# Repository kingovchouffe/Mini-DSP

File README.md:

# Mini-DSP

Mini-DSP is an audio-effects hardware and firmware project built around the
ES8388 audio codec and Raspberry Pi RP2350.

## Hardware

The KiCad designs include the main RP2350A/ES8388 board in
[`HW/Main`](HW/Main/) and an ES8388 test board in
[`Test board`](Test%20board/). They provide schematic and PCB references for
the codec, I2S audio interface, and supporting circuitry. See
[`HW/Main/README.md`](HW/Main/README.md) for hardware notes; confirm board
revisions and pin mappings before wiring.

## Software

[`SW/arduino_i2s_loopback`](SW/arduino_i2s_loopback/) contains an Arduino-Pico
full-duplex I2S sketch for the RP2350 and ES8388. It captures the mono input,
applies a time-based effect, and sends the result to the codec output. A
three-way DIP switch selects among bypass, chorus, flanger, delay, and reverb
presets. The effects and preset mapping are in separate header files.

See [`SW/README.md`](SW/README.md) for setup, wiring considerations, presets,
and build instructions.

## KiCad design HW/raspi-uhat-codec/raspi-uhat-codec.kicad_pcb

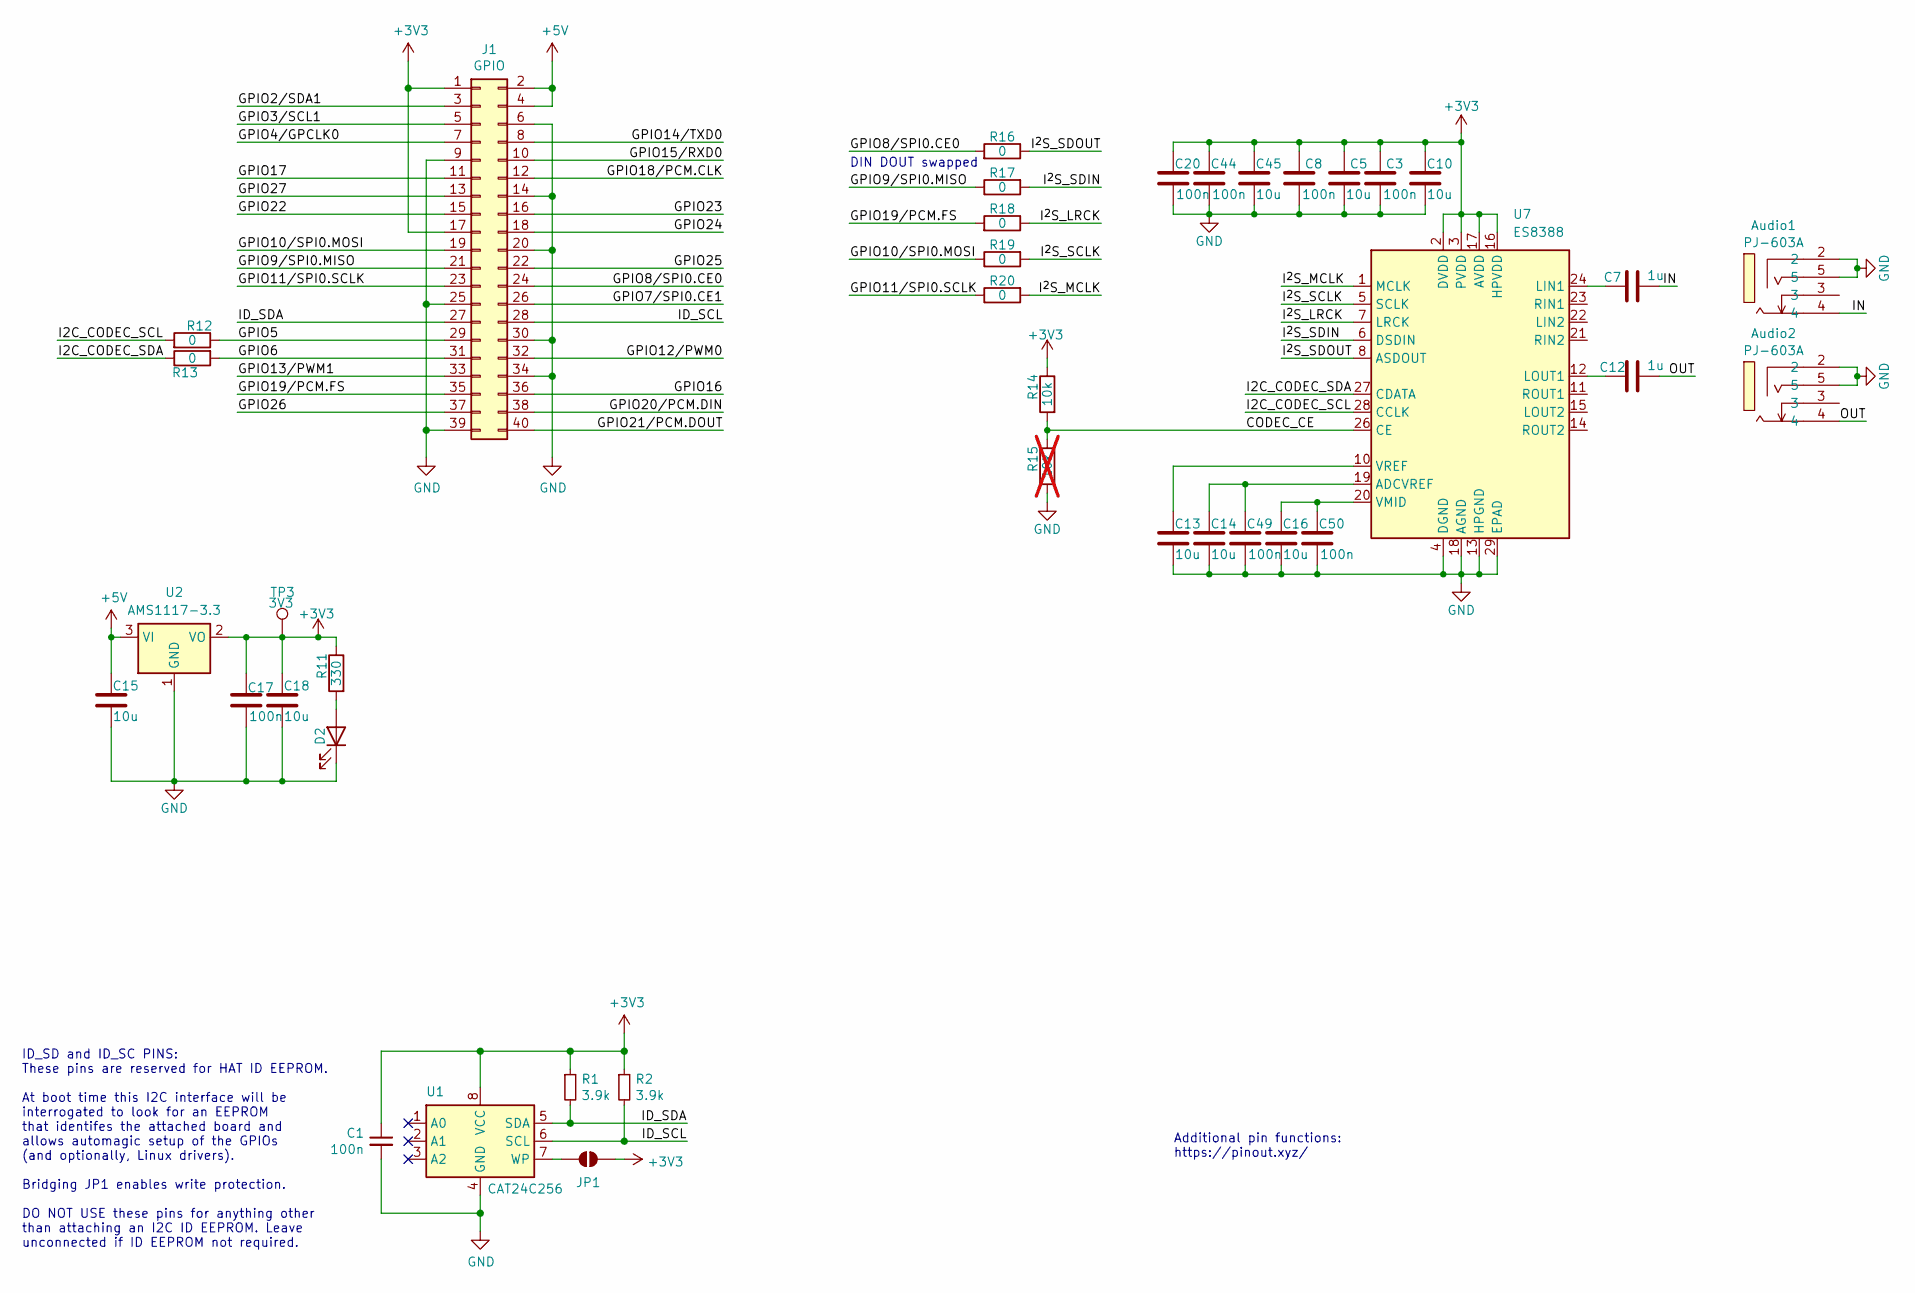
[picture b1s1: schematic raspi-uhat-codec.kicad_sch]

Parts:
Audio1, Audio2: PJ-603A; AUDIO-TH_PJ-603A_1; LCSC Part C309273
C1, C3, C8, C17, C20, C44, C49, C50: 100n; C_0603_1608Metric
C5, C10, C13, C14, C15, C16, C18, C45: 10u; C_0603_1608Metric
C7, C12: 1u; C_0805_2012Metric
D2: CTL1; LED_0805_2012Metric
J1: GPIO; PinSocket_2x20_P2.54mm_Vertical
JP1: ID_WP; SolderJumper-2_P1.3mm_Open_TrianglePad1.0x1.5mm
R1, R2: 3.9k; R_0603_1608Metric
R11: 330; R_0603_1608Metric
R12, R13, R16, R17, R18, R19, R20: 0; R_0603_1608Metric
R14: 10k; R_0603_1608Metric
R15: 10k; R_0603_1608Metric; not fitted
TP3: 3V3; TestPoint_Pad_D1.0mm
U1: CAT24C256; SOIC-8_3.9x4.9mm_P1.27mm
U2: AMS1117-3.3; SOT-223-3_TabPin2
U7: ES8388; QFN-28-1EP_4x4mm_P0.45mm_EP2.6x2.6mm

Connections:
+3V3: C1.1, C3.1, C5.1, C8.1, C10.1, C17.1, C18.1, C20.1, C44.1, C45.1, J1.1, J1.17, JP1.2 (B), R1.1, R2.1, R11.1, R14.1, TP3.1 (1_1), U1.8 (VCC), U2.2 (VO), U7.2 (DVDD), U7.3 (PVDD), U7.16 (HPVDD), U7.17 (AVDD)
+5V: C15.1, J1.2, J1.4, U2.3 (VI)
/CODEC_CE: R14.2, R15.1, U7.26 (CE)
/GPIO2/SDA1: J1.3
/GPIO3/SCL1: J1.5
/GPIO4/GPCLK0: J1.7
/GPIO5: J1.29, R12.1
/GPIO6: J1.31, R13.2
/GPIO7/SPI0.CE1: J1.26
/GPIO8/SPI0.CE0: J1.24, R16.2
/GPIO9/SPI0.MISO: J1.21, R17.1
/GPIO10/SPI0.MOSI: J1.19, R19.1
/GPIO11/SPI0.SCLK: J1.23, R20.1
/GPIO12/PWM0: J1.32
/GPIO13/PWM1: J1.33
/GPIO14/TXD0: J1.8
/GPIO15/RXD0: J1.10
/GPIO16: J1.36
/GPIO17: J1.11
/GPIO18/PCM.CLK: J1.12
/GPIO19/PCM.FS: J1.35, R18.2
/GPIO20/PCM.DIN: J1.38
/GPIO21/PCM.DOUT: J1.40
/GPIO22: J1.15
/GPIO23: J1.16
/GPIO24: J1.18
/GPIO25: J1.22
/GPIO26: J1.37
/GPIO27: J1.13
/I2C_CODEC_SCL: R12.2, U7.28 (CCLK)
/I2C_CODEC_SDA: R13.1, U7.27 (CDATA)
/ID_SCL: J1.28, R2.2, U1.6 (SCL)
/ID_SDA: J1.27, R1.2, U1.5 (SDA)
/IN: Audio1.4, C7.2
/I^{2}S_LRCK: R18.1, U7.7 (LRCK)
/I^{2}S_MCLK: R20.2, U7.1 (MCLK)
/I^{2}S_SCLK: R19.2, U7.5 (SCLK)
/I^{2}S_SDIN: R17.2, U7.6 (DSDIN)
/I^{2}S_SDOUT: R16.1, U7.8 (ASDOUT)
/OUT: Audio2.4, C12.2
GND: Audio1.2, Audio1.5, Audio2.2, Audio2.5, C1.2, C3.2, C5.2, C8.2, C10.2, C13.2, C14.2, C15.2, C16.2, C17.2, C18.2, C20.2, C44.2, C45.2, C49.2, C50.2, D2.1 (K), J1.6, J1.9, J1.14, J1.20, J1.25, J1.30, J1.34, J1.39, R15.2, U1.4 (GND), U2.1 (GND), U7.4 (DGND), U7.13 (HPGND), U7.18 (AGND), U7.29 (EPAD)
unnamed: D2.2 (A), R11.2
unnamed: JP1.1 (A), U1.7 (WP)
unnamed: C14.1, C49.1, U7.19 (ADCVREF)
unnamed: C7.1, U7.24 (LIN1)
unnamed: C12.1, U7.12 (LOUT1)
unnamed: C16.1, C50.1, U7.20 (VMID)
unnamed: C13.1, U7.10 (VREF)

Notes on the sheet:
ID_SD and ID_SC PINS: These pins are reserved for HAT ID EEPROM. At boot time this I2C interface will be interrogated to look for an EEPROM that identifes the attached board and allows automagic setup of the GPIOs (and optionally, Linux drivers). Bridging JP1 enables write protection. DO NOT USE th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
DIN DOUT swapped
Additional pin functions: https://pinout.xyz/

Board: 2 copper layers, 43 parts (1 on the bottom side), 29 nets, no tracks yet.

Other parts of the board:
MH1, MH2, MH3, MH4: MountingHole_2.7mm_M2.5

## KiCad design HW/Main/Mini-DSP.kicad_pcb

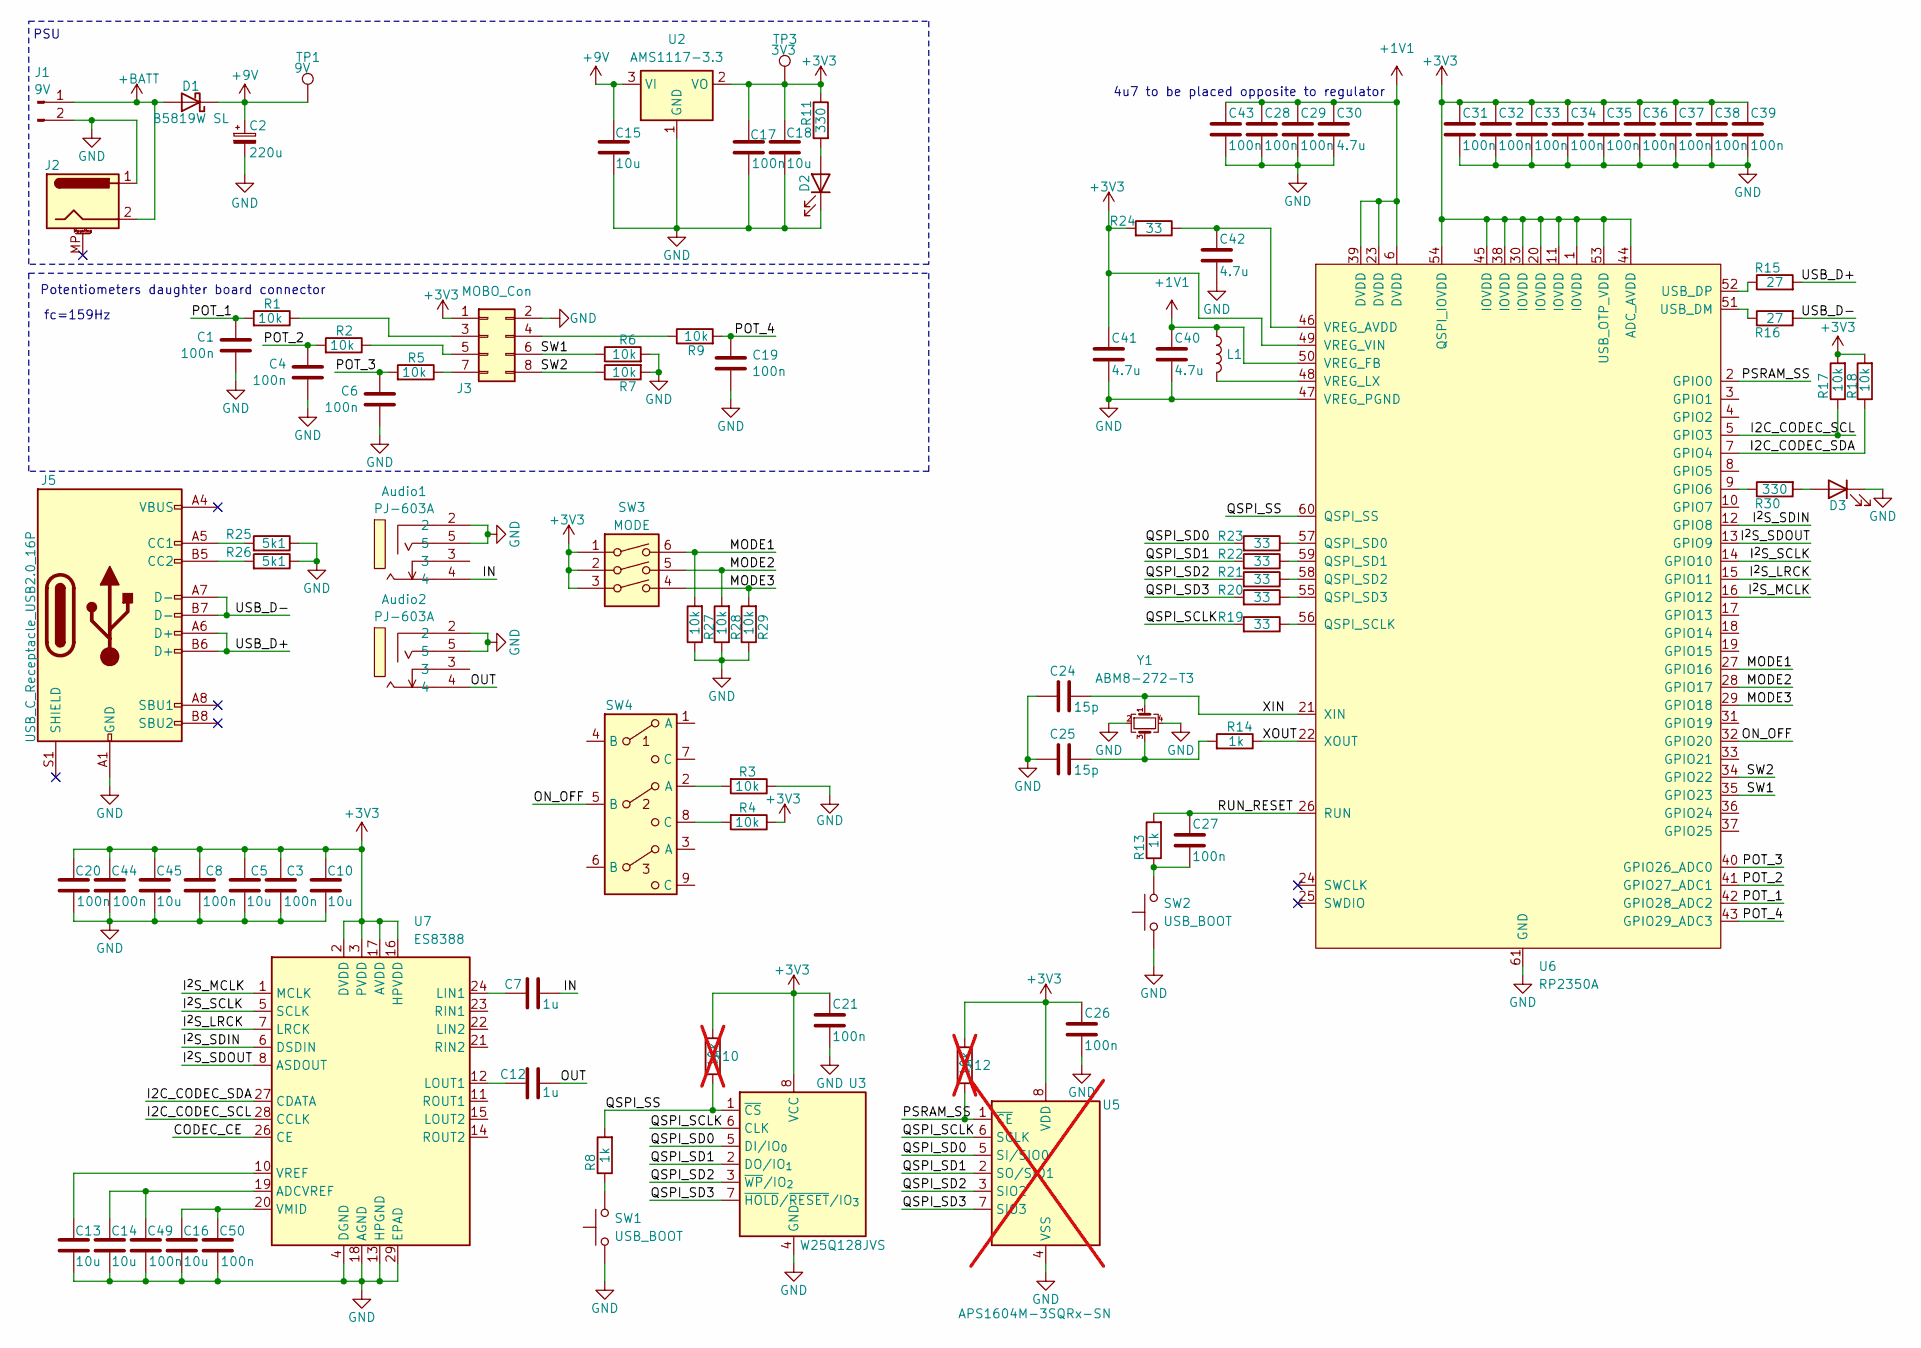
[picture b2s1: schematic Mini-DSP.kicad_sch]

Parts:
Audio1, Audio2: PJ-603A; AUDIO-TH_PJ-603A_1; LCSC Part C309273
C1, C3, C4, C6, C8, C17, C19, C20, C21, C26, C27, C28, C29, C31, C32, C33, C34, C35, C36, C37, C38, C39, C43, C44, C49, C50: 100n; C_0402_1005Metric
C2: 220u; CP_Elec_6.3x7.7
C5, C10, C13, C14, C15, C16, C18, C45: 10u; C_0603_1608Metric
C7, C12: 1u; C_0805_2012Metric
C24, C25: 15p; C_0402_1005Metric
C30, C40, C41, C42: 4.7u; C_0402_1005Metric
D1: B5819W SL; D_SOD-323; JLCPCB Part C8598
D2, D3: CTL1; LED_0603_1608Metric
J1: 9V; PinSocket_1x02_P2.54mm_Vertical
J2: Barrel_Jack_MountingPin; BarrelJack_Horizontal
J3: MOBO_Con; PinSocket_2x04_P2.54mm_Vertical
J5: USB_C_Receptacle_USB2.0_16P; USB_C_Receptacle_HCTL_HC-TYPE-C-16P-01A
L1: AOTA-B201610S3R3-101-T; L_Murata_DFE201610P
R1, R2, R3, R4, R5, R6, R7, R9, R17, R18, R27, R28, R29: 10k; R_0402_1005Metric
R8, R13, R14: 1k; R_0402_1005Metric
R10, R12: 10k; R_0402_1005Metric; not fitted
R11, R30: 330; R_0402_1005Metric
R15, R16: 27; R_0402_1005Metric
R19, R20, R21, R22, R23, R24: 33; R_0402_1005Metric
R25, R26: 5k1; R_0402_1005Metric
SW1, SW2: USB_BOOT; SW_SPST_TS-1088-xR020
SW3: MODE; SW_DIP_SPSTx03_Slide_KingTek_DSHP03TS_W7.62mm_P1.27mm
SW4: 3PDT_LED
TP1: 9V; TestPoint_Pad_D1.0mm
TP3: 3V3; TestPoint_Pad_D1.0mm
U2: AMS1117-3.3; SOT-223-3_TabPin2
U3: W25Q128JVS; SOIC-8_5.3x5.3mm_P1.27mm
U5: APS1604M-3SQRx-SN; SOIC-8_3.9x4.9mm_P1.27mm; not fitted
U6: RP2350A; QFN-60-1EP_7x7mm_P0.4mm_EP3.4x3.4mm_ThermalVias
U7: ES8388; QFN-28-1EP_4x4mm_P0.45mm_EP2.6x2.6mm
Y1: ABM8-272-T3; Crystal_SMD_3225-4Pin_3.2x2.5mm

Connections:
+1V1: C28.1, C29.1, C30.1, C40.1, C43.1, L1.1, U6.6 (DVDD), U6.23 (DVDD), U6.39 (DVDD), U6.50 (VREG_FB)
+3V3: C3.1, C5.1, C8.1, C10.1, C17.1, C18.1, C20.1, C21.1, C26.1, C31.1, C32.1, C33.1, C34.1, C35.1, C36.1, C37.1, C38.1, C39.1, C41.1, C44.1, C45.1, J3.1, R4.1, R10.2, R11.1, R12.2, R17.2, R18.2, R24.2, SW3.1, SW3.2, SW3.3, TP3.1 (1_1), U2.2 (VO), U3.8 (VCC), U5.8 (VDD), U6.1 (IOVDD), U6.11 (IOVDD), U6.20 (IOVDD), U6.30 (IOVDD), U6.38 (IOVDD), U6.44 (ADC_AVDD), U6.45 (IOVDD), U6.49 (VREG_VIN), U6.53 (USB_OTP_VDD), U6.54 (QSPI_IOVDD), U7.2 (DVDD), U7.3 (PVDD), U7.16 (HPVDD), U7.17 (AVDD)
+9V: C2.1, C15.1, D1.1 (K), TP1.1 (1_1), U2.3 (VI)
+BATT: D1.2 (A), J1.1, J2.2
/CODEC_CE: U7.26 (CE)
/I2C_CODEC_SCL: R17.1, U6.5 (GPIO3), U7.28 (CCLK)
/I2C_CODEC_SDA: R18.1, U6.7 (GPIO4), U7.27 (CDATA)
/IN: Audio1.4, C7.2
/I^{2}S_LRCK: U6.15 (GPIO11), U7.7 (LRCK)
/I^{2}S_MCLK: U6.16 (GPIO12), U7.1 (MCLK)
/I^{2}S_SCLK: U6.14 (GPIO10), U7.5 (SCLK)
/I^{2}S_SDIN: U6.12 (GPIO8), U7.6 (DSDIN)
/I^{2}S_SDOUT: U6.13 (GPIO9), U7.8 (ASDOUT)
/MODE1: R27.2, SW3.6, U6.27 (GPIO16)
/MODE2: R28.2, SW3.5, U6.28 (GPIO17)
/MODE3: R29.2, SW3.4, U6.29 (GPIO18)
/ON_OFF: SW4.5 (B), U6.32 (GPIO20)
/OUT: Audio2.4, C12.2
/POT_1: C1.1, R1.2, U6.42 (GPIO28_ADC2)
/POT_2: C4.1, R2.2, U6.41 (GPIO27_ADC1)
/POT_3: C6.1, R5.2, U6.40 (GPIO26_ADC0)
/POT_4: C19.1, R9.2, U6.43 (GPIO29_ADC3)
/PSRAM_SS: R12.1, U5.1 (~CE), U6.2 (GPIO0)
/QSPI_SCLK: R19.2, U3.6 (CLK), U5.6 (SCLK)
/QSPI_SD0: R23.2, U3.5 (DI/IO_{0}), U5.5 (SI/SIO0)
/QSPI_SD1: R22.2, U3.2 (DO/IO_{1}), U5.2 (SO/SIO1)
/QSPI_SD2: R21.2, U3.3 (~WP/IO_{2}), U5.3 (SIO2)
/QSPI_SD3: R20.2, U3.7 (~HOLD/~RESET/IO_{3}), U5.7 (SIO3)
/QSPI_SS: R8.2, R10.1, U3.1 (~CS), U6.60 (QSPI_SS)
/RUN_RESET: C27.1, R13.2, U6.26 (RUN)
/SW1: J3.6, R6.1, U6.35 (GPIO23)
/SW2: J3.8, R7.1, U6.34 (GPIO22)
/USB_D+: J5.A6 (D+), J5.B6 (D+), R15.2
/USB_D-: J5.A7 (D-), J5.B7 (D-), R16.2
/XIN: C24.2, U6.21 (XIN), Y1.1
/XOUT: R14.1, U6.22 (XOUT)
GND: Audio1.2, Audio1.5, Audio2.2, Audio2.5, C1.2, C2.2, C3.2, C4.2, C5.2, C6.2, C8.2, C10.2, C13.2, C14.2, C15.2, C16.2, C17.2, C18.2, C19.2, C20.2, C21.2, C24.1, C25.1, C26.2, C28.2, C29.2, C30.2, C31.2, C32.2, C33.2, C34.2, C35.2, C36.2, C37.2, C38.2, C39.2, C40.2, C41.2, C42.2, C43.2, C44.2, C45.2, C49.2, C50.2, D2.1 (K), D3.1 (K), J1.2, J2.1, J3.2, J5.A1 (GND), J5.A12 (GND), J5.B1 (GND), J5.B12 (GND), R3.1, R6.2, R7.2, R25.1, R26.1, R27.1, R28.1, R29.1, SW1.1, SW2.1, U2.1 (GND), U3.4 (GND), U5.4 (VSS), U6.47 (VREG_PGND), U6.61 (GND), U7.4 (DGND), U7.13 (HPGND), U7.18 (AGND), U7.29 (EPAD), Y1.2, Y1.4
unnamed: C25.2, R14.2, Y1.3
unnamed: C27.2, R13.1, SW2.2
unnamed: D2.2 (A), R11.2
unnamed: D3.2 (A), R30.2
unnamed: J3.3, R1.1
unnamed: J3.4, R9.1
unnamed: J3.5, R2.1
unnamed: J3.7, R5.1
unnamed: J5.A5 (CC1), R25.2
unnamed: J5.B5 (CC2), R26.2
unnamed: R3.2, SW4.2 (A)
unnamed: R4.2, SW4.8 (C)
unnamed: R8.1, SW1.2
unnamed: R30.1, U6.9 (GPIO6)
unnamed: R19.1, U6.56 (QSPI_SCLK)
unnamed: R23.1, U6.57 (QSPI_SD0)
unnamed: R22.1, U6.59 (QSPI_SD1)
unnamed: R21.1, U6.58 (QSPI_SD2)
unnamed: R20.1, U6.55 (QSPI_SD3)
unnamed: R16.1, U6.51 (USB_DM)
unnamed: R15.1, U6.52 (USB_DP)
unnamed: C42.1, R24.1, U6.46 (VREG_AVDD)
unnamed: L1.2, U6.48 (VREG_LX)
unnamed: C14.1, C49.1, U7.19 (ADCVREF)
unnamed: C7.1, U7.24 (LIN1)
unnamed: C12.1, U7.12 (LOUT1)
unnamed: C16.1, C50.1, U7.20 (VMID)
unnamed: C13.1, U7.10 (VREF)

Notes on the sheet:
4u7 to be placed opposite to regulator
PSU
fc=159Hz
Potentiometers daughter board connector

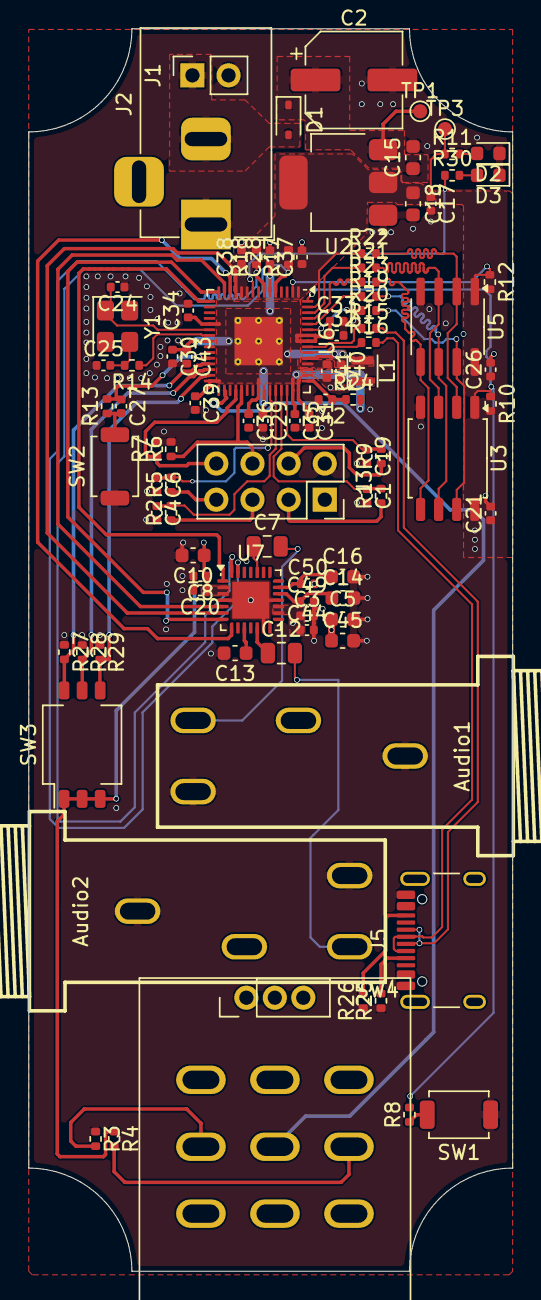
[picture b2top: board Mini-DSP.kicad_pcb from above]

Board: 4 copper layers, 34.0 x 87.3 mm, 95 parts (0 on the bottom side), 64 nets.

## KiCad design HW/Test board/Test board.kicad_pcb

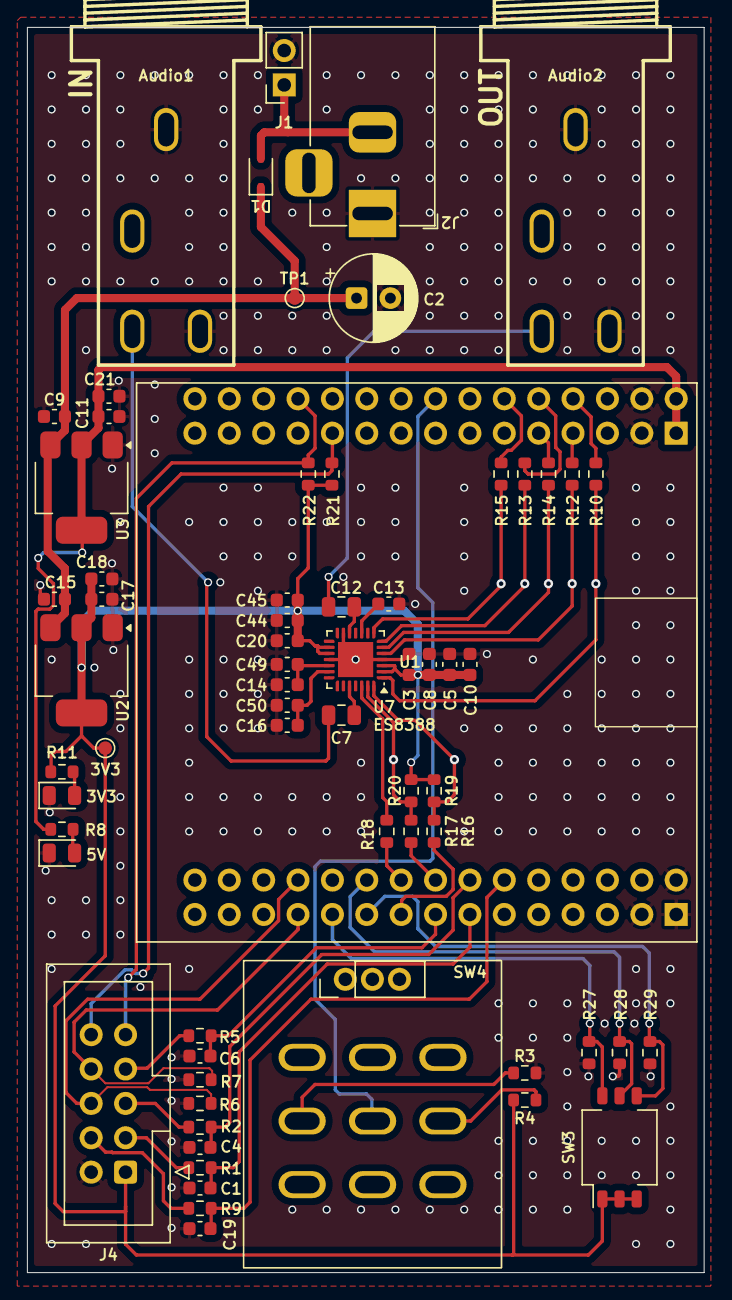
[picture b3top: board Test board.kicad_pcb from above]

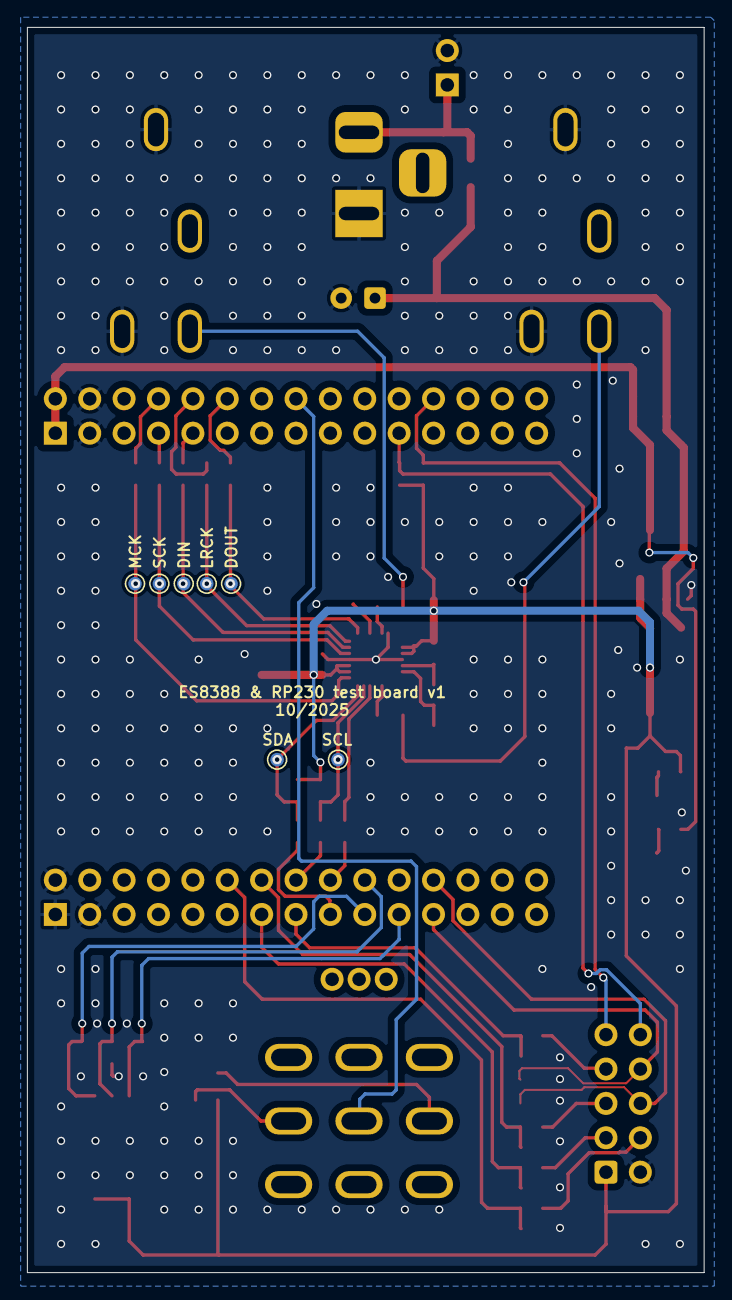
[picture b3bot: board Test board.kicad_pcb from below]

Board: 2 copper layers, 50.0 x 92.0 mm, 73 parts (7 on the bottom side), 48 nets.

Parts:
Audio1, Audio2: PJ-603A; AUDIO-TH_PJ-603A_1
C1, C3, C4, C6, C8, C11, C17, C19, C20, C44, C49, C50: 100n; C_0603_1608Metric
C2: 220u; CP_Radial_D6.3mm_P2.50mm
C5, C9, C10, C13, C14, C15, C16, C18, C21, C45: 10u; C_0603_1608Metric
C7, C12: 1u; C_0805_2012Metric
D1: B5819W SL; D_SOD-323
D2, D3: CTL1; LED_0805_2012Metric
J1: 9V; PinSocket_1x02_P2.54mm_Vertical
J2: Barrel_Jack_MountingPin; BarrelJack_Horizontal
J4: MOBO; IDC-Header_2x05_P2.54mm_Vertical
R1, R2, R3, R4, R5, R6, R7, R9, R19, R20, R21, R22, R27, R28, R29: 10k; R_0603_1608Metric
R8, R11: 330; R_0603_1608Metric
R10, R12, R13, R14, R15, R16, R17, R18: 0; R_0603_1608Metric
SW3: MODE; SW_DIP_SPSTx03_Slide_KingTek_DSHP03TS_W7.62mm_P1.27mm
SW4: 3PDT_LED
TP1: 9V; TestPoint_Pad_D1.0mm
TP2, TP4, TP5, TP6, TP7, TP8, TP9: TestPoint_Pad_D1.0mm
TP3: 3V3; TestPoint_Pad_D1.0mm
U1: WeAct2550B
U2: AMS1117-3.3; SOT-223-3_TabPin2
U3: AMS1117-5.0; SOT-223-3_TabPin2
U7: ES8388; QFN-28-1EP_4x4mm_P0.45mm_EP2.6x2.6mm

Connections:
+3V3: C3.1, C5.1, C8.1, C10.1, C17.1, C18.1, C20.1, C44.1, C45.1, J4.1, R4.1, R11.1, R19.2, R20.2, R21.2, R22.2, SW3.1, SW3.2, SW3.3, TP3.1, U2.2 (VO), U7.2 (DVDD), U7.3 (PVDD), U7.16 (HPVDD), U7.17 (AVDD)
+5V: C11.1, C21.1, R8.1, U1.5V, U1.VBUS, U3.2 (VO)
+9V: C2.1, C9.1, C15.1, D1.1 (K), TP1.1, U2.3 (VI), U3.3 (VI)
+BATT: D1.2 (A), J1.1, J2.2
/CODEC_CE: R18.1, U7.26 (CE)
/I2C_CODEC_SCL: R17.1, R20.1, TP9.1, U7.27 (CDATA)
/I2C_CODEC_SDA: R16.1, R19.1, TP8.1, U7.28 (CCLK)
/I2C_SCREEN_SCL: J4.9, R22.1, U1.17 (GP17)
/I2C_SCREEN_SDA: J4.10, R21.1, U1.16 (GP16)
/IN: Audio1.4, C7.2
/I^{2}S_LRCK: R13.1, TP5.1, U7.7 (LRCK)
/I^{2}S_MCLK: R10.1, TP2.1, U7.1 (MCLK)
/I^{2}S_SCLK: R12.1, TP4.1, U7.5 (SCLK)
/I^{2}S_SDIN: R14.1, TP6.1, U7.6 (DSDIN)
/I^{2}S_SDOUT: R15.1, TP7.1, U7.8 (ASDOUT)
/MODE1: R27.2, SW3.6, U1.34 (GP34)
/MODE2: R28.2, SW3.5, U1.35 (GP35)
/MODE3: R29.2, SW3.4, U1.36 (GP36)
/ON_OFF: SW4.5 (B), U1.9 (GP9)
/OUT: Audio2.4, C12.2
/POT_1: C1.1, R1.2, U1.42 (GP42)
/POT_2: C4.1, R2.2, U1.41 (GP41)
/POT_3: C6.1, R5.2, U1.40 (GP40)
/POT_4: C19.1, R9.2, U1.43 (GP43)
/SW1: J4.6, R6.1, U1.31 (GP31)
/SW2: J4.8, R7.1, U1.32 (GP32)
GND: Audio1.2, Audio1.5, Audio2.2, Audio2.5, C1.2, C2.2, C3.2, C4.2, C5.2, C6.2, C8.2, C9.2, C10.2, C11.2, C13.2, C14.2, C15.2, C16.2, C17.2, C18.2, C19.2, C20.2, C21.2, C44.2, C45.2, C49.2, C50.2, D2.1 (K), D3.1 (K), J1.2, J2.1, J4.2, R3.1, R6.2, R7.2, R27.1, R28.1, R29.1, U1.G (GND), U2.1 (GND), U3.1 (GND), U7.4 (DGND), U7.13 (HPGND), U7.18 (AGND), U7.29 (EPAD)
unnamed: D2.2 (A), R11.2
unnamed: D3.2 (A), R8.2
unnamed: J4.3, R1.1
unnamed: J4.4, R9.1
unnamed: J4.5, R2.1
unnamed: J4.7, R5.1
unnamed: R3.2, SW4.2 (A)
unnamed: R4.2, SW4.8 (C)
unnamed: R10.2, U1.1 (GP1)
unnamed: R12.2, U1.2 (GP2)
unnamed: R13.2, U1.3 (GP3)
unnamed: R14.2, U1.4 (GP4)
unnamed: R15.2, U1.5 (GP5)
unnamed: R18.2, U1.37 (GP37)
unnamed: R16.2, U1.38 (GP38)
unnamed: R17.2, U1.39 (GP39)
unnamed: C14.1, C49.1, U7.19 (ADCVREF)
unnamed: C7.1, U7.24 (LIN1)
unnamed: C12.1, U7.12 (LOUT1)
unnamed: C16.1, C50.1, U7.20 (VMID)
unnamed: C13.1, U7.10 (VREF)

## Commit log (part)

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2025-09-21 update schematic and placement
    - missing 3PDT part
    - need to change CS4270 (EoL)
2025-09-28 test board update
